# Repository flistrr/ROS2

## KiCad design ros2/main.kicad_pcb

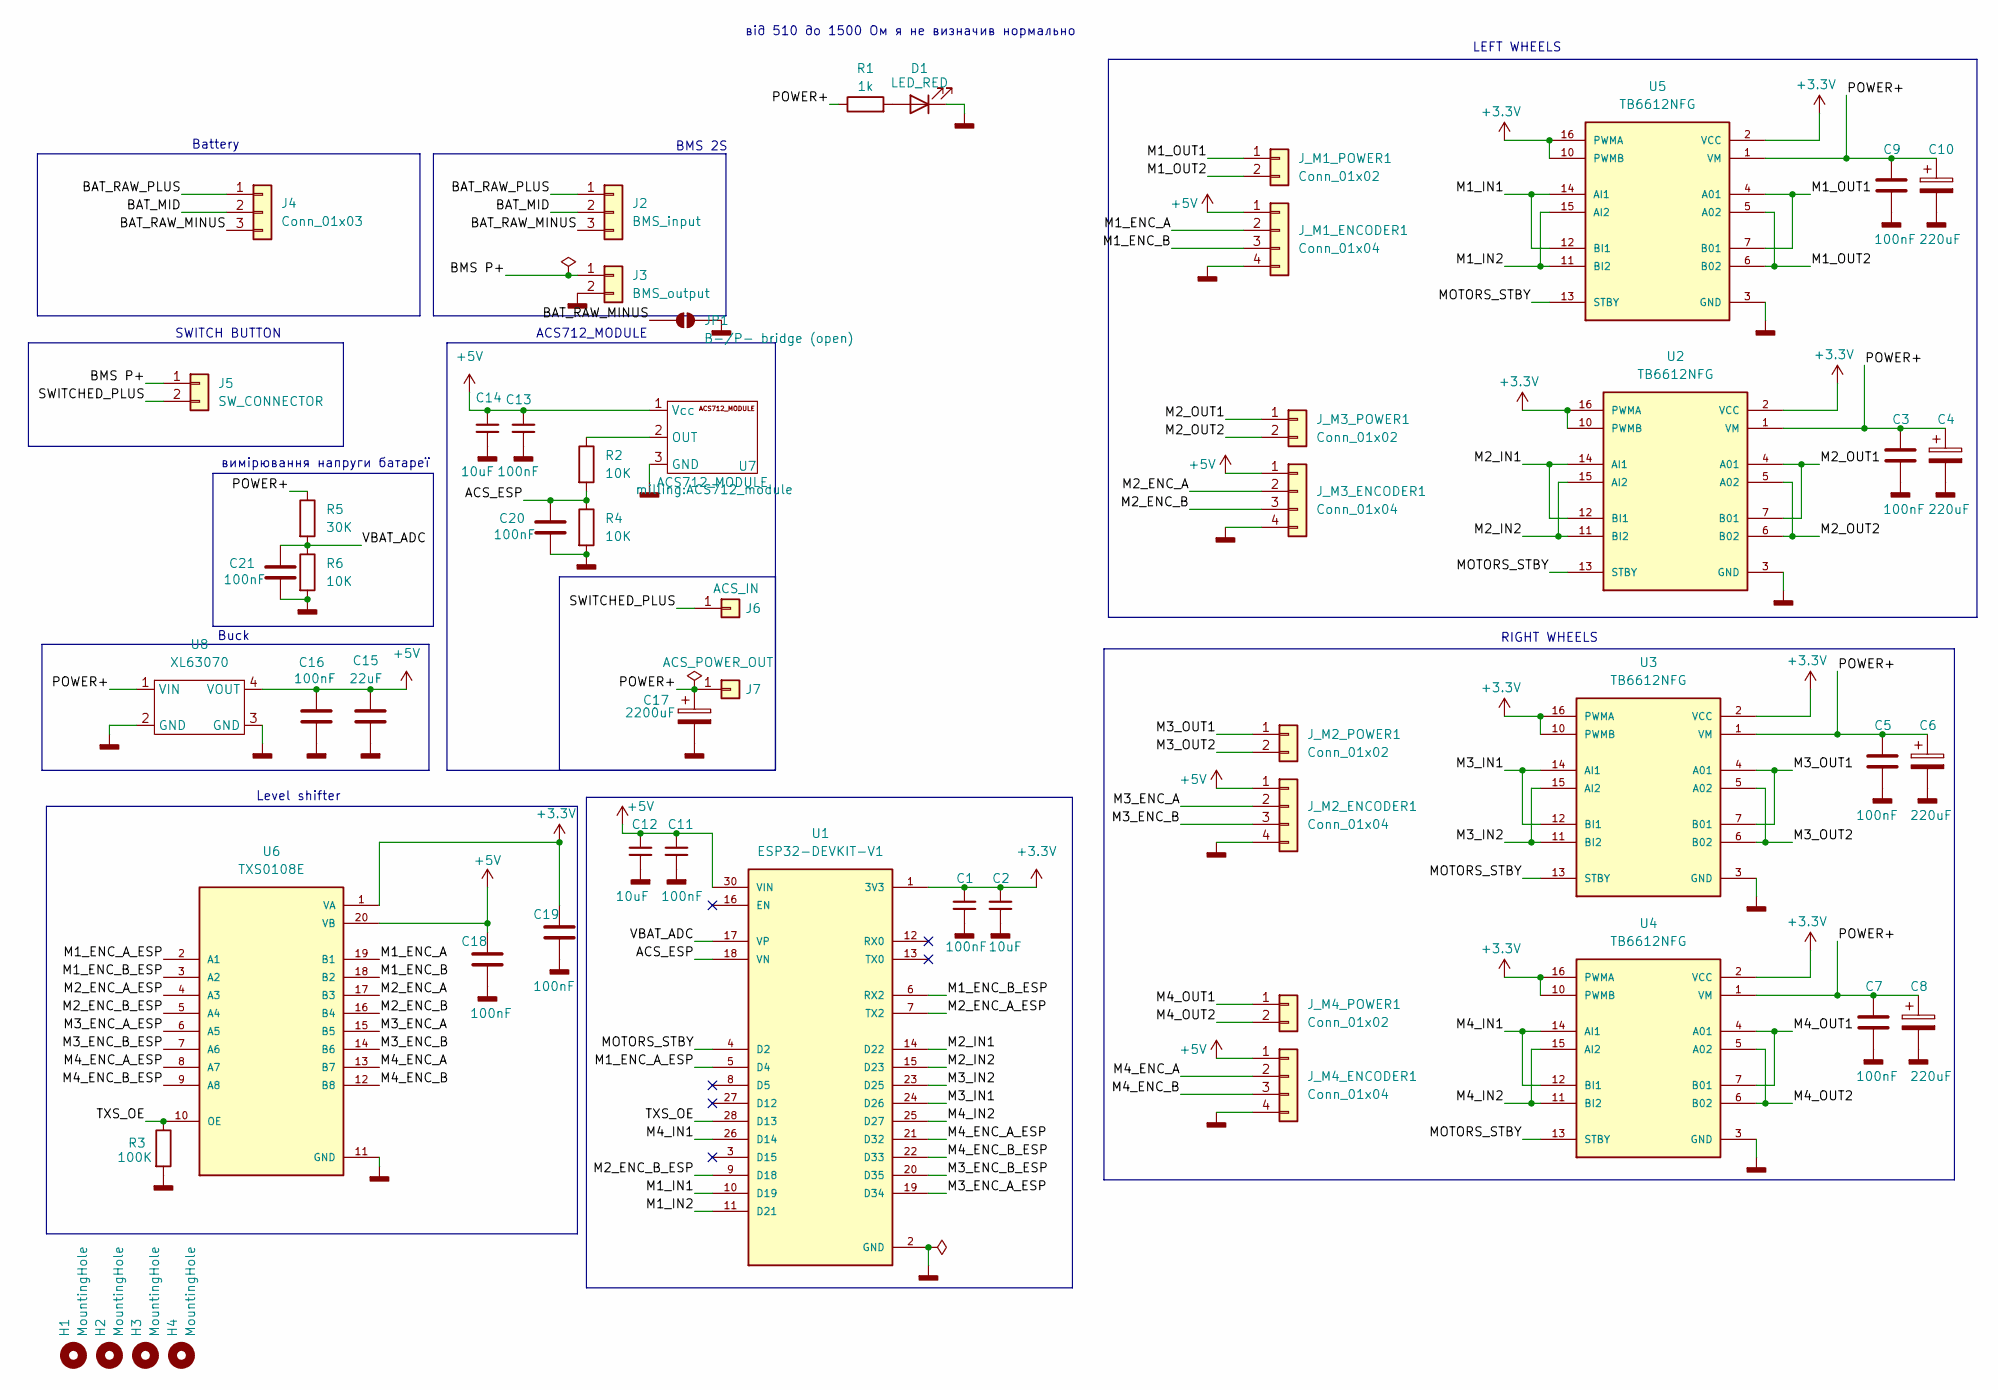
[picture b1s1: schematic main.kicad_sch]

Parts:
C1, C3, C5, C7, C9, C11, C13, C16, C18, C19, C20, C21: 100nF; C_Disc_D5.0mm_W2.5mm_P5.00mm
C2, C12, C14: 10uF; C_Disc_D5.0mm_W2.5mm_P5.00mm
C4, C6, C8, C10: 220uF; CP_Radial_D10.0mm_P3.50mm
C15: 22uF; C_Disc_D5.0mm_W2.5mm_P5.00mm
C17: 2200uF; CP_Radial_D12.5mm_P5.00mm
D1: LED_RED; LED_D5.0mm
H1, H2, H3, H4: MountingHole; MountingHole_3.2mm_M3
J2: BMS_input; SolderWire-1sqmm_1x03_P5.4mm_D1.4mm_OD2.7mm
J3: BMS_output; SolderWire-1sqmm_1x02_P5.4mm_D1.4mm_OD2.7mm
J4: Conn_01x03; SolderWire-1sqmm_1x03_P5.4mm_D1.4mm_OD2.7mm
J5: SW_CONNECTOR; SolderWire-1sqmm_1x02_P5.4mm_D1.4mm_OD2.7mm
J6: ACS_IN; SolderWire-1sqmm_1x01_D1.4mm_OD2.7mm
J7: ACS_POWER_OUT; SolderWire-1sqmm_1x01_D1.4mm_OD2.7mm
JP1: B-/P- bridge (open); PinHeader_1x02_P2.54mm_Vertical
J_M1_ENCODER1, J_M2_ENCODER1, J_M3_ENCODER1, J_M4_ENCODER1: Conn_01x04; PinHeader_1x04_P2.54mm_Vertical
J_M1_POWER1, J_M2_POWER1, J_M3_POWER1, J_M4_POWER1: Conn_01x02; PinHeader_1x02_P2.54mm_Vertical
R1: 1k; R_Axial_DIN0207_L6.3mm_D2.5mm_P7.62mm_Horizontal
R2: 10К; R_Axial_DIN0207_L6.3mm_D2.5mm_P7.62mm_Horizontal
R3: 100K; R_Axial_DIN0207_L6.3mm_D2.5mm_P7.62mm_Horizontal
R4, R6: 10K; R_Axial_DIN0207_L6.3mm_D2.5mm_P7.62mm_Horizontal
R5: 30К; R_Axial_DIN0207_L6.3mm_D2.5mm_P7.62mm_Horizontal
U1: ESP32-DEVKIT-V1; MODULE_ESP32_DEVKIT_V1_38P_NEW; PARTREV N/A
U2, U3, U4, U5: TB6612NFG; MODULE_ROB-14450; PARTREV 11-13-17
U6: TXS0108E; MODULE_ZC323900; PARTREV NA
U7: ACS712_MODULE; ACS712_module
U8: XL63070; XL63070_Module_30x16

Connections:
+3.3V: C1.1, C2.1, C19.1, U1.1 (3V3), U2.2 (VCC), U2.10 (PWMB), U2.16 (PWMA), U3.2 (VCC), U3.10 (PWMB), U3.16 (PWMA), U4.2 (VCC), U4.10 (PWMB), U4.16 (PWMA), U5.2 (VCC), U5.10 (PWMB), U5.16 (PWMA), U6.1 (VA)
+5V: C11.1, C12.1, C13.1, C14.1, C15.1, C16.1, C18.1, J_M1_ENCODER1.1, J_M2_ENCODER1.1, J_M3_ENCODER1.1, J_M4_ENCODER1.1, U1.30 (VIN), U6.20 (VB), U7.1 (Vcc), U8.4 (VOUT)
/ACS_ESP: C20.1, R2.2, R4.1, U1.18 (VN)
/BAT_MID: J2.2, J4.2
/BAT_RAW_MINUS: J2.3, J4.3, JP1.1 (A)
/BAT_RAW_PLUS: J2.1, J4.1
/BMS P+: J3.1, J5.1
/M1_ENC_A: J_M1_ENCODER1.2, U6.19 (B1)
/M1_ENC_A_ESP: U1.5 (D4), U6.2 (A1)
/M1_ENC_B: J_M1_ENCODER1.3, U6.18 (B2)
/M1_ENC_B_ESP: U1.6 (RX2), U6.3 (A2)
/M1_IN1: U1.10 (D19), U5.12 (BI1), U5.14 (AI1)
/M1_IN2: U1.11 (D21), U5.11 (BI2), U5.15 (AI2)
/M1_OUT1: J_M1_POWER1.1, U5.4 (A01), U5.7 (B01)
/M1_OUT2: J_M1_POWER1.2, U5.5 (A02), U5.6 (B02)
/M2_ENC_A: J_M3_ENCODER1.2, U6.17 (B3)
/M2_ENC_A_ESP: U1.7 (TX2), U6.4 (A3)
/M2_ENC_B: J_M3_ENCODER1.3, U6.16 (B4)
/M2_ENC_B_ESP: U1.9 (D18), U6.5 (A4)
/M2_IN1: U1.14 (D22), U2.12 (BI1), U2.14 (AI1)
/M2_IN2: U1.15 (D23), U2.11 (BI2), U2.15 (AI2)
/M2_OUT1: J_M3_POWER1.1, U2.4 (A01), U2.7 (B01)
/M2_OUT2: J_M3_POWER1.2, U2.5 (A02), U2.6 (B02)
/M3_ENC_A: J_M2_ENCODER1.2, U6.15 (B5)
/M3_ENC_A_ESP: U1.19 (D34), U6.6 (A5)
/M3_ENC_B: J_M2_ENCODER1.3, U6.14 (B6)
/M3_ENC_B_ESP: U1.20 (D35), U6.7 (A6)
/M3_IN1: U1.24 (D26), U3.12 (BI1), U3.14 (AI1)
/M3_IN2: U1.23 (D25), U3.11 (BI2), U3.15 (AI2)
/M3_OUT1: J_M2_POWER1.1, U3.4 (A01), U3.7 (B01)
/M3_OUT2: J_M2_POWER1.2, U3.5 (A02), U3.6 (B02)
/M4_ENC_A: J_M4_ENCODER1.2, U6.13 (B7)
/M4_ENC_A_ESP: U1.21 (D32), U6.8 (A7)
/M4_ENC_B: J_M4_ENCODER1.3, U6.12 (B8)
/M4_ENC_B_ESP: U1.22 (D33), U6.9 (A8)
/M4_IN1: U1.26 (D14), U4.12 (BI1), U4.14 (AI1)
/M4_IN2: U1.25 (D27), U4.11 (BI2), U4.15 (AI2)
/M4_OUT1: J_M4_POWER1.1, U4.4 (A01), U4.7 (B01)
/M4_OUT2: J_M4_POWER1.2, U4.5 (A02), U4.6 (B02)
/MOTORS_STBY: U1.4 (D2), U2.13 (STBY), U3.13 (STBY), U4.13 (STBY), U5.13 (STBY)
/POWER+: C3.1, C4.1, C5.1, C6.1, C7.1, C8.1, C9.1, C10.1, C17.1, J7.1 (Pin_1_1), R1.1, R5.1, U2.1 (VM), U3.1 (VM), U4.1 (VM), U5.1 (VM), U8.1 (VIN)
/SWITCHED_PLUS: J5.2, J6.1 (Pin_1_1)
/TXS_OE: R3.1, U1.28 (D13), U6.10 (OE)
/VBAT_ADC: C21.1, R5.2, R6.1, U1.17 (VP)
GNDD: C1.2, C2.2, C3.2, C4.2, C5.2, C6.2, C7.2, C8.2, C9.2, C10.2, C11.2, C12.2, C13.2, C14.2, C15.2, C16.2, C17.2, C18.2, C19.2, C20.2, C21.2, D1.1 (K), J3.2, JP1.2 (B), J_M1_ENCODER1.4, J_M2_ENCODER1.4, J_M3_ENCODER1.4, J_M4_ENCODER1.4, R3.2, R4.2, R6.2, U1.2 (GND), U1.29 (GND), U2.3 (GND), U2.8 (GND), U2.9 (GND), U3.3 (GND), U3.8 (GND), U3.9 (GND), U4.3 (GND), U4.8 (GND), U4.9 (GND), U5.3 (GND), U5.8 (GND), U5.9 (GND), U6.11 (GND), U7.3 (GND), U8.2 (GND), U8.3 (GND)
unnamed: D1.2 (A), R1.2
unnamed: R2.1, U7.2 (OUT)

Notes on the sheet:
Level shifter
RIGHT WHEELS
ACS712_MODULE
BMS 2S
SWITCH BUTTON
Battery
Buck
LEFT WHEELS
вимірювання напруги батареї
від 510 до 1500 Ом я не визначив нормально

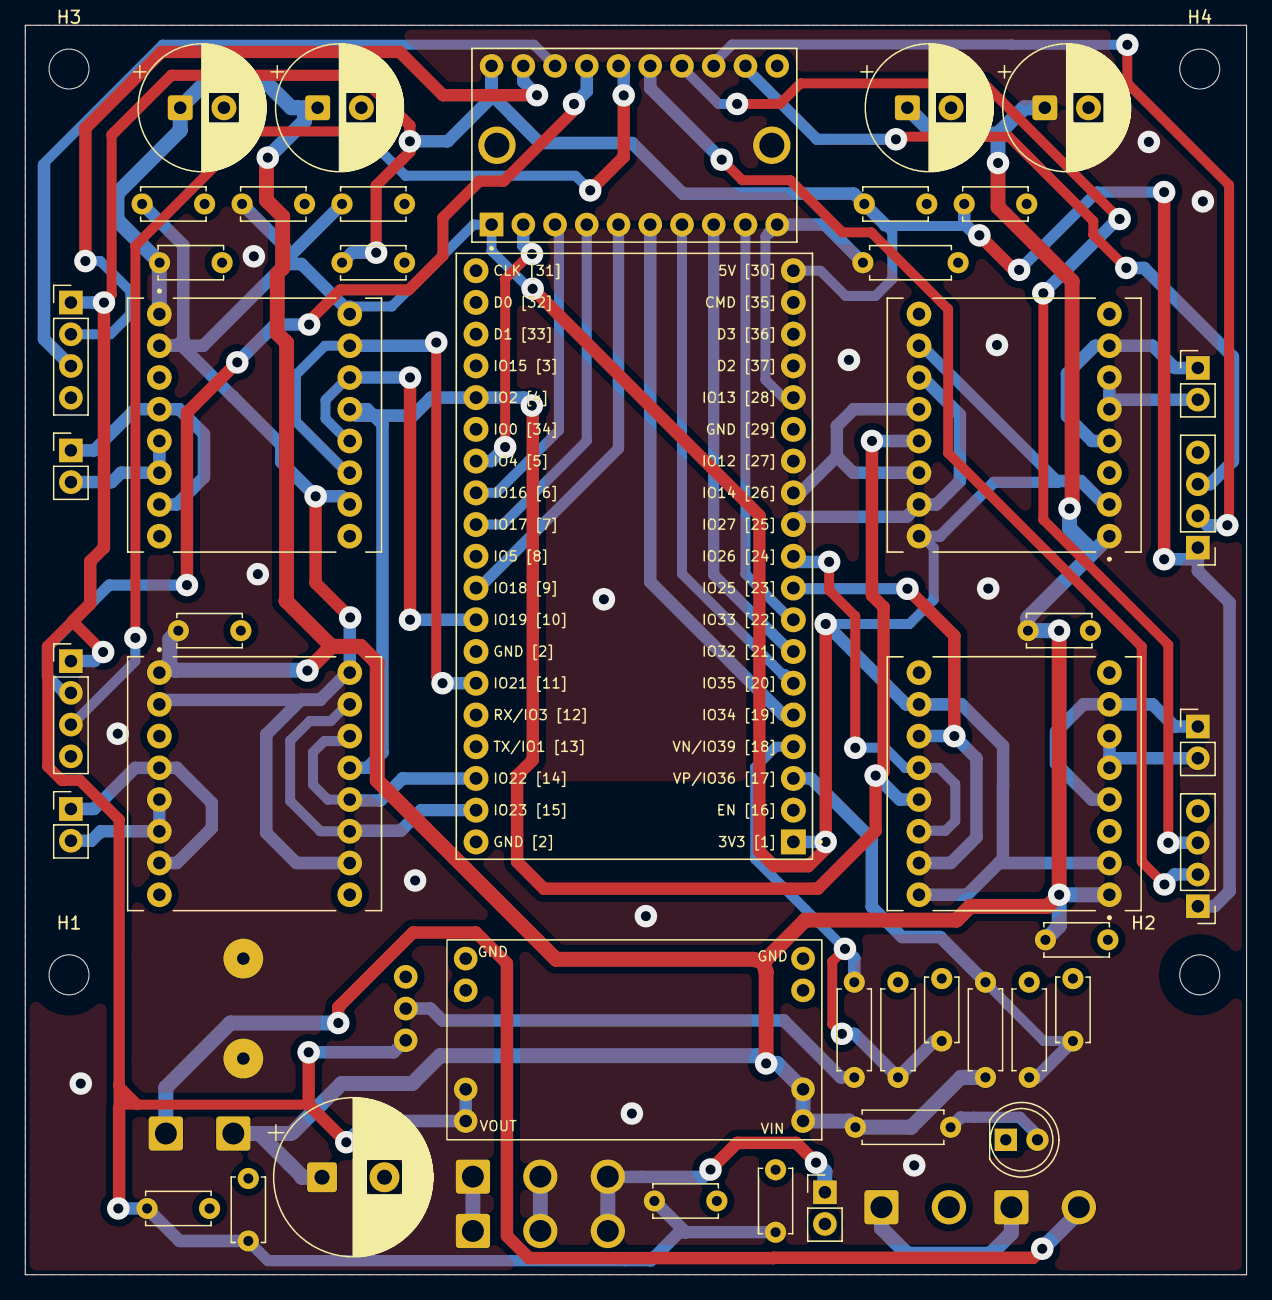
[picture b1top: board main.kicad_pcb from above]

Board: 2 copper layers, 97.8 x 100.0 mm, 55 parts (0 on the bottom side), 47 nets.
